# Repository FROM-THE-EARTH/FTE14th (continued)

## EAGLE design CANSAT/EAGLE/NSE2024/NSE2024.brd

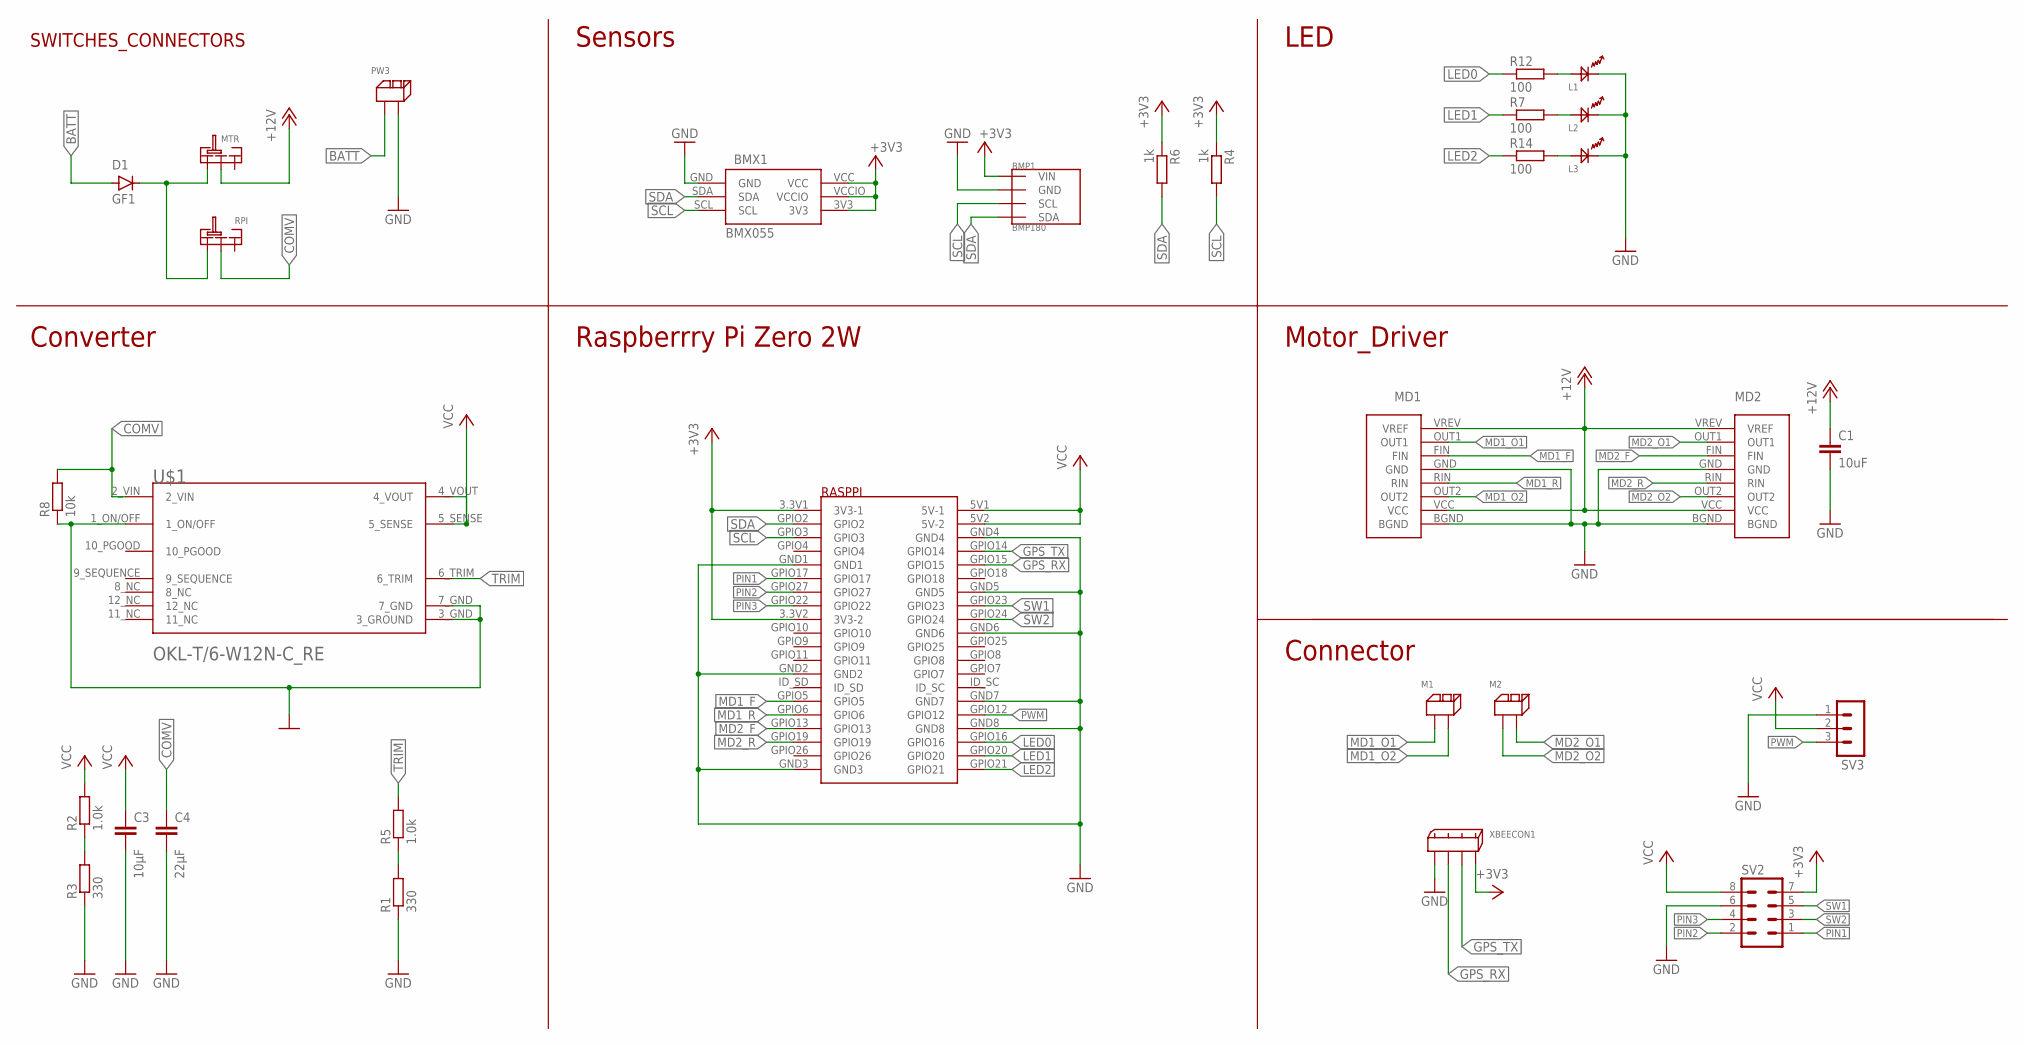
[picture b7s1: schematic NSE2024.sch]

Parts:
BMP1: BMP180; GY-68
BMX1: BMX055
C1: 10uF; C0603
C3: 10μF; C0603
C4: 22μF; C0805
D1: GF1; SMA-DO214AC
L1, L2, L3: OSXX1608C1A
M1, M2: 2PIN
MD1, MD2: BD6222HFP-TR
MTR: SRIDE_SWITCH
PW3: 2PIN
R1, R3: 330; R0603
R2, R5: 1.0k; R0603
R4, R6: 1k; R0603
R7, R12, R14: 100; R0603
R8: 10k; R0603
RASPPI: RASPBERYPIZEROW
RPI: SRIDE_SWITCH
SV2: MA04-2
SV3: MA03-1
U$1: OKL-T/6-W12N-C_RE; MURATA_IKL-T-6-W12N-C_0_RECOMENDED
XBEECON1: 2.5_MINI-SPOX_4PIN

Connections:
+3V3: BMP1.P1 (VIN), BMX1.3V3, BMX1.VCC, BMX1.VCCIO, R4.1, R6.1, RASPPI.3.3V1 (3V3-1), RASPPI.3.3V2 (3V3-2), SV2.7, XBEECON1.P$4 (4)
+5V: C3.1, U$1.4_VOUT, U$1.5_SENSE
+12V: C1.1, MD1.VCC, MD1.VREV (VREF), MD2.VCC, MD2.VREV (VREF), MTR.LR
BATT: D1.A, PW3.P$1
COMV: C4.1, R8.2, RPI.LR, U$1.2_VIN
GND: BMP1.P2 (GND), BMX1.GND, C1.2, C3.2, C4.2, L1.CT, L2.CT, L3.CT, MD1.BGND, MD1.GND, MD2.BGND, MD2.GND, PW3.P$2, R1.1, R3.1, R8.1, RASPPI.GND1, RASPPI.GND2, RASPPI.GND3, RASPPI.GND4, RASPPI.GND5, RASPPI.GND6, RASPPI.GND7, RASPPI.GND8, SV2.6, SV3.1, U$1.1_ON/OFF, U$1.3_GND (3_GROUND), U$1.7_GND, XBEECON1.P$1 (1)
GPS_RX: RASPPI.GPIO15, XBEECON1.P$2 (2)
GPS_TX: RASPPI.GPIO14, XBEECON1.P$3 (3)
LED0: R12.1, RASPPI.GPIO16
LED1: R7.1, RASPPI.GPIO20
LED2: R14.1, RASPPI.GPIO21
MD1_F: MD1.FIN, RASPPI.GPIO5
MD1_O1: M1.P$1, MD1.OUT1
MD1_O2: M1.P$2, MD1.OUT2
MD1_R: MD1.RIN, RASPPI.GPIO6
MD2_F: MD2.FIN, RASPPI.GPIO13
MD2_O1: M2.P$2, MD2.OUT1
MD2_O2: M2.P$1, MD2.OUT2
MD2_R: MD2.RIN, RASPPI.GPIO19
unnamed: R1.2, R5.1
unnamed: R2.1, R3.2
unnamed: L1.AN, R12.2
unnamed: D1.K (C), MTR.L, RPI.L
unnamed: L3.AN, R14.2
unnamed: L2.AN, R7.2
PIN1: RASPPI.GPIO17, SV2.1
PIN2: RASPPI.GPIO27, SV2.2
PIN3: RASPPI.GPIO22, SV2.4
PWM: RASPPI.GPIO12, SV3.3
SCL: BMP1.P3 (SCL), BMX1.SCL, R4.2, RASPPI.GPIO3
SDA: BMP1.P4 (SDA), BMX1.SDA, R6.2, RASPPI.GPIO2
SW1: RASPPI.GPIO23, SV2.5
SW2: RASPPI.GPIO24, SV2.3
TRIM: R5.2, U$1.6_TRIM
VCC: R2.2, RASPPI.5V1 (5V-1), RASPPI.5V2 (5V-2), SV2.8, SV3.2

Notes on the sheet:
SWITCHES_CONNECTORS
Sensors
Converter
Motor_Driver
LED
Connector
Raspberrry Pi Zero 2W

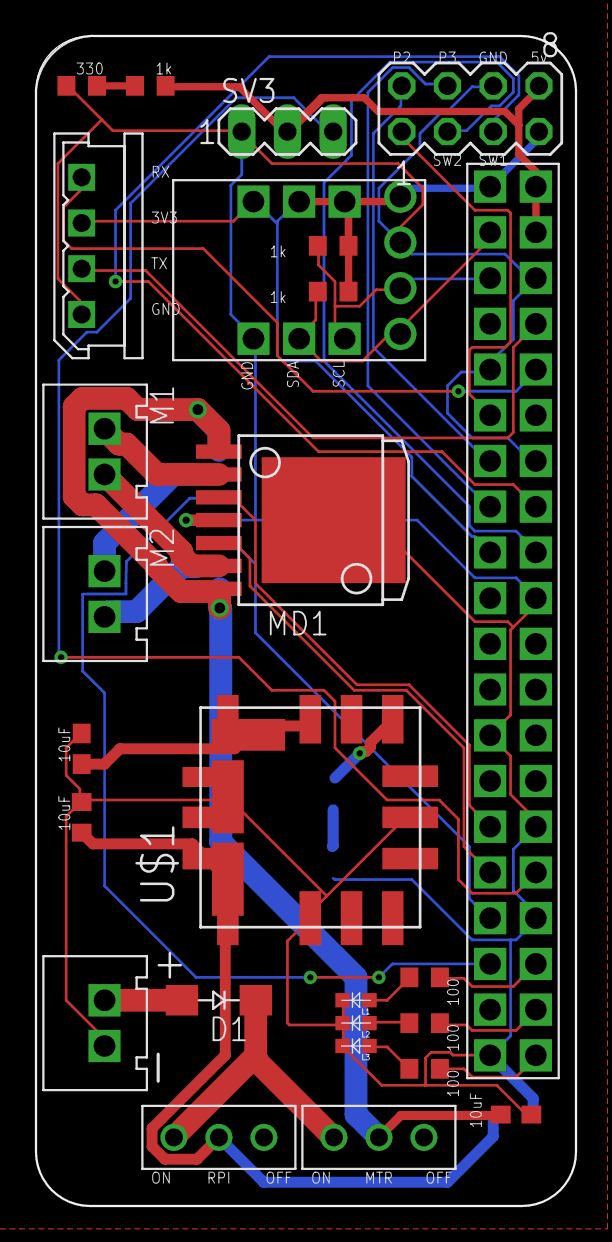
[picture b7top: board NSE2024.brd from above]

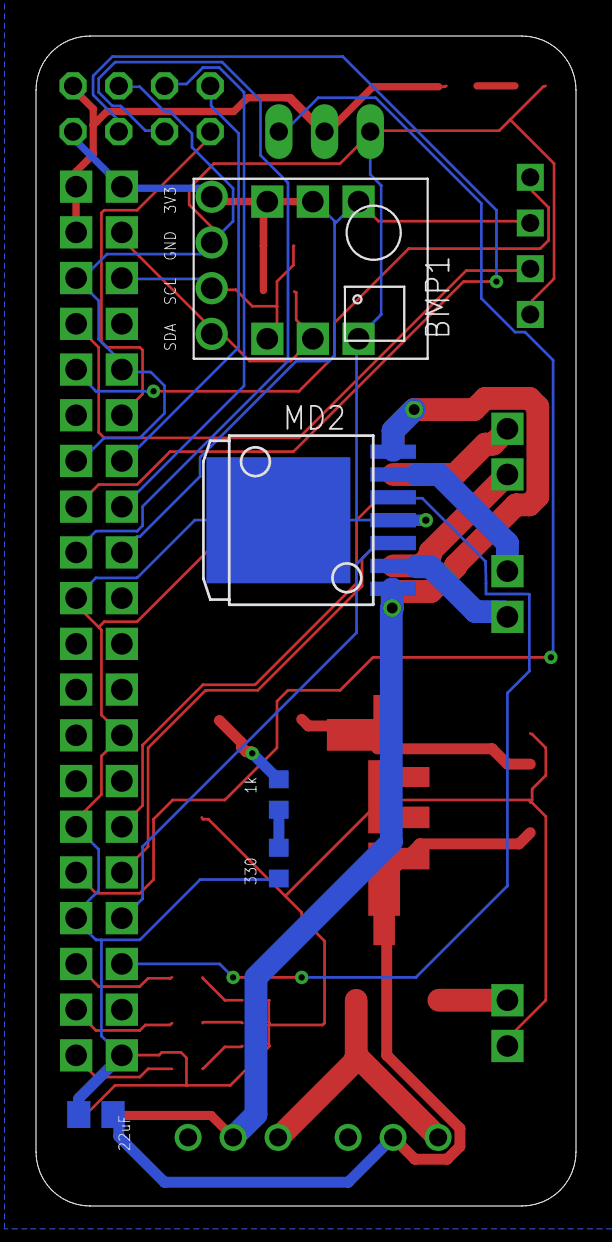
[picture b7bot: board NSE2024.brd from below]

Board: 2 copper layers, 30.0 x 65.0 mm, 31 parts (5 on the bottom side), 35 nets.

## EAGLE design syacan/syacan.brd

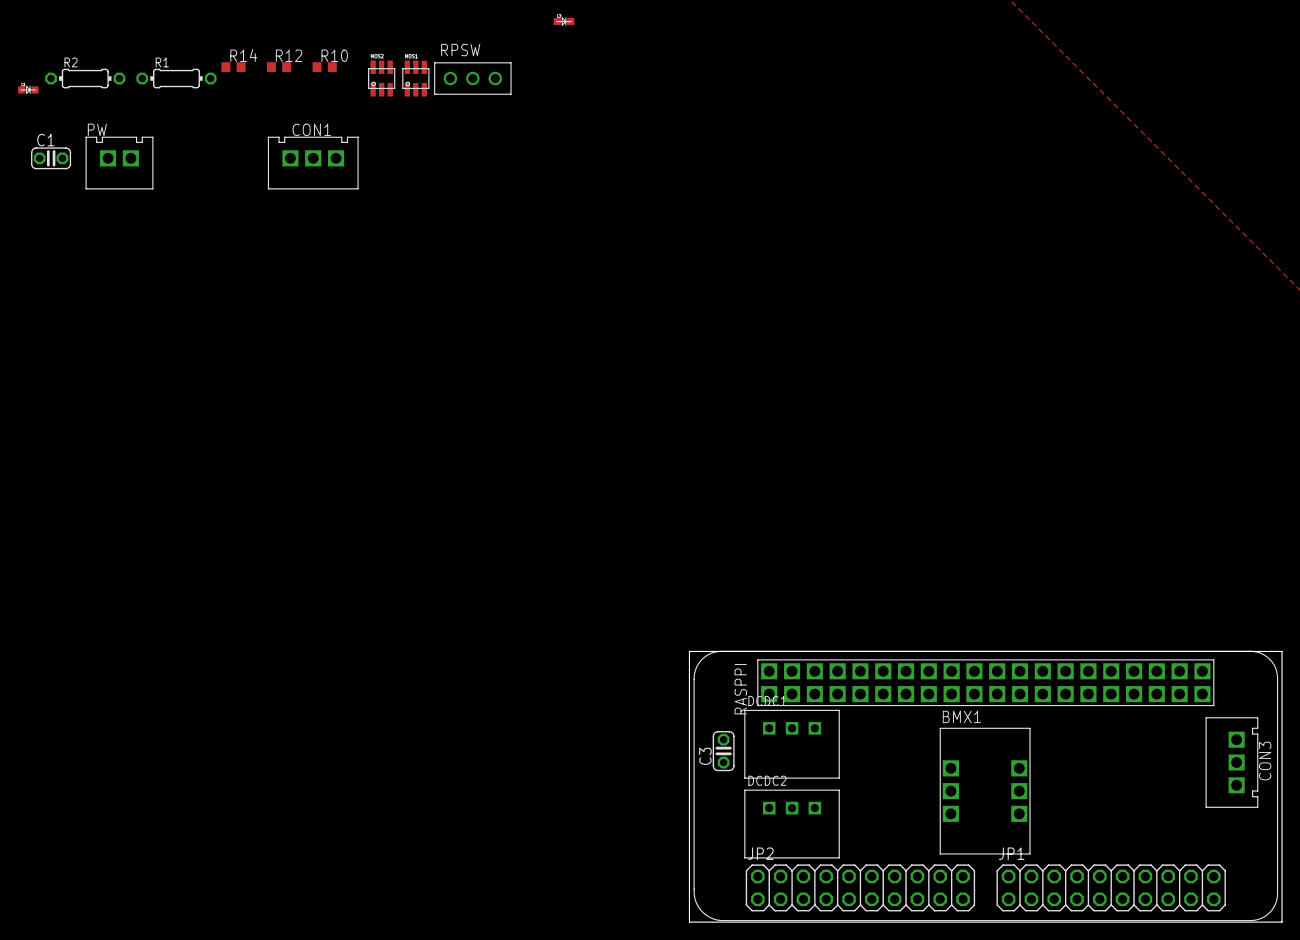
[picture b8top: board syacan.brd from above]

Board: 2 copper layers, 66.0 x 30.1 mm, 21 parts (0 on the bottom side), 35 nets, no tracks yet.

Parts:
BMX1: BMX055
C1, C3: 3.3uF; C025-024X044
CON1, CON3: 3PIN
DCDC1, DCDC2: 3.3V1A_M78AR033-1
JP1, JP2: 2X10
L1, L3: OSXX1608C1A
MOS1, MOS2: SSM6J808R
PW: 2PIN
R1, R2: 4.7k; 0204/7
R10: 100k; R0603
R12, R14: 100; R0603
RASPPI: RASPBERYPIZEROW
RPSW: SRIDE_SWITCH

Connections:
+3V3: C1.1, DCDC1.VOUT, JP2.1, RASPPI.3.3V1, RASPPI.3.3V2
+5V: BMX1.VCC, C3.1, CON1.P$2, CON3.P$2, DCDC1.VIN, DCDC2.VOUT, JP2.2, R1.2, R2.2, RASPPI.5V1, RASPPI.5V2
+7.4V: MOS2.1, MOS2.2, MOS2.5, MOS2.6
BATT: MOS1.1, MOS1.2, MOS1.5, MOS1.6, PW.P$2
GND: BMX1.GND, C1.2, C3.2, CON1.P$3, CON3.P$3, DCDC1.GND, DCDC2.GND, JP2.5, JP2.6, JP2.7, JP2.8, L1.CT, L3.CT, MOS1.3, PW.P$1, RASPPI.GND1, RASPPI.GND2, RASPPI.GND3, RASPPI.GND4, RASPPI.GND5, RASPPI.GND6, RASPPI.GND7, RPSW.LR
GPIO4: JP1.1, RASPPI.GPIO4
GPIO5: JP1.3, RASPPI.GPIO5
GPIO6: JP1.5, RASPPI.GPIO6
GPIO7: JP1.7, RASPPI.GPIO7
GPIO8: JP1.9, RASPPI.GPIO8
GPIO9: JP1.11, RASPPI.GPIO9
GPIO10: JP1.13, RASPPI.GPIO10
GPIO11: JP1.15, RASPPI.GPIO11
GPIO13: JP1.2, RASPPI.GPIO13
GPIO14: JP1.4, RASPPI.GPIO14
GPIO15: JP1.6, RASPPI.GPIO15
GPIO16: JP1.8, RASPPI.GPIO16
GPIO17: JP1.10, RASPPI.GPIO17
GPIO19: JP1.12, RASPPI.GPIO19
GPIO20: JP1.16, RASPPI.GPIO20
GPIO21: JP1.14, RASPPI.GPIO21
GPIO23: JP1.17, RASPPI.GPIO23
GPIO24: JP1.19, RASPPI.GPIO24
GPIO25: JP1.18, RASPPI.GPIO25
GPIO27: JP1.20, RASPPI.GPIO27
LED0: R12.1, RASPPI.GPIO22
LED2: R14.1, RASPPI.GPIO26
unnamed: L1.AN, R12.2
unnamed: L3.AN, R14.2
unnamed: MOS1.4, MOS2.4, R10.2
unnamed: MOS2.3, R10.1, RPSW.L
SCL: BMX1.SCL, JP2.11, R1.1, RASPPI.GPIO3
SDA: BMX1.SDA, JP2.9, R2.1, RASPPI.GPIO2
SV0: CON3.P$1, RASPPI.GPIO12
SV2: CON1.P$1, RASPPI.GPIO18

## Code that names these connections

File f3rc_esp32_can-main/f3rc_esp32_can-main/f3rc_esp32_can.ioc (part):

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Mcu.Name=STM32G474R(B-C-E)Tx
Mcu.Package=LQFP64
Mcu.UserName=STM32G474RBTx
PA11.Mode=FDCAN_Activate
PA11.Signal=FDCAN1_RX
PA12.Mode=FDCAN_Activate
PA12.Signal=FDCAN1_TX
PA2.Mode=Asynchronous
PA2.Signal=USART2_TX
PA3.Mode=Asynchronous
PA3.Signal=USART2_RX
PC4.Mode=Asynchronous
PC4.Signal=USART1_TX
PC5.Mode=Asynchronous
PC5.Signal=USART1_RX
RCC.HSE_VALUE=8000000
RCC.SYSCLKFreq_VALUE=80000000
RCC.SYSCLKSource=RCC_SYSCLKSOURCE_PLLCLK
board=custom

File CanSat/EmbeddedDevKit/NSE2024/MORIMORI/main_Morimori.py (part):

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DATA_SAMPLING_RATE = 0.00001
ALTITUDE_CONST1 = 30
ALTITUDE_CONST2 = 5
SERVO_PIN = 12
LED0 = 25
LED1 = 8
LED2 = 7
HIGH = 1
LOW = 0
M1A = 13
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
bmx = BMX055.BMX055()
bmp = BMP085.BMP085()
servo = pigpio.pi()

nowTime = datetime.datetime.now()
fileName = '/home/karisora/FTE14/NiCs2024/log/testlog_' + nowTime.strftime('%Y-%m%d-%H%M%S') + '.csv'
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    bmx.setUp()

    GPIO.setmode(GPIO.BCM)
    GPIO.setup(LED1, GPIO.OUT)
    GPIO.setup(LED2, GPIO.OUT)
   #GPIO.setup(SW1, GPIO.IN, pull_up_down=GPIO.PUD_DOWN)
   #GPIO.setup(SW2, GPIO.IN, pull_up_down=GPIO.PUD_DOWN)
    GPIO.setup(Heating_wire, GPIO.OUT)          
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    roi_img = cv2.cvtColor(roi_img, cv2.COLOR_BGR2RGB)
    detector.set_roi_img(roi_img)

    GPIO.output(LED2, HIGH)
    print("Setup OK")


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            after = currentMilliTime()
        if (max[1] - min[1]) > 20 and (max[2] - min[2] > 20):
            print("calibration(): Complete!")
            GPIO.output(LED1, HIGH)
            complete = True
            time.sleep(1)
            calibBias[1] = (max[1] + min[1]) / 2
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
            calibRange[1] = (max[1] - min[1]) / 2
            calibRange[2] = (max[2] - min[2]) / 2
            GPIO.output(LED1, LOW)
            time.sleep(2)


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    # 角度を500から2500のパルス幅にマッピングする
    pulse_width = (angle / 180) * (2500 - 500) + 500
    # パルス幅を設定してサーボを回転させる
    servo.set_servo_pulsewidth(SERVO_PIN, pulse_width)

def LED_Checker(num):
    for _ in range(num):
        GPIO.output(LED1, HIGH)
        time.sleep(0.1)
        GPIO.output(LED1, LOW)
        time.sleep(0.1)


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
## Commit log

2023-11-13 ki
    k
2023-11-14 test
2023-11-16 ver1.1
2023-11-19 Create NiCs_cansat
2023-11-27 Create NiCs2024
2023-11-27 rename
2023-11-27 ver1.3
2023-12-21 opencv_test を更新
2024-02-15 Create ISE2024_14thboard#1.1.b##
2024-03-16 add remote_main.py
2024-03-29 a
    a
2024-03-30 upload result files
2024-04-05 カラーコーン到達判定を改良・コメント付記
2024-04-26 q
    a
2024-05-06 i
    u
2024-05-12 NiCs2024の基盤追加
2024-05-12 ファイル整理
2024-05-12 NSE2024基盤追加
2024-06-04 board追加
2024-06-24 Create dengen1.2.sch
    new dengen
2024-06-25 n ew
2024-06-27 Checked and created board file
2024-06-27 Created dengen board file
2024-06-27 Board changed
2024-06-27 328修正
2024-06-28 2枚版追加
2024-06-30 Changed dengen board
2024-07-02 changed board files
2024-07-03 Changed board file
2024-07-03 Changed board
2024-07-04 Completed board files ver1.0
2024-07-04 ver1.1 uploaded
2024-07-04 ver1.2
2024-07-05 Added via
2024-07-10 add readme about raspi setup
2024-07-12 readme
2024-07-12 k
    k
2024-07-12 add readme
2024-07-12 completed datalogger 4.1
2024-07-13 completed ver4.1
2024-07-14 changed v4.2
2024-07-16 ver4.1 flight model
2024-07-16 add excel and .Rmd file for flightdata analysis
2024-08-06 NSE2024
2024-08-06 cv2 add
2024-08-06 stuck試し
2024-08-06 added
2024-08-07 Flag
2024-08-07 Flag_v2
2024-08-09 timeout.v1
2024-08-09 morimori
2024-08-12 add modified Prologue
2024-08-23 fix file structures
2024-08-23 Upload ipynb files for aerodynamics
2024-09-05 フォトカプラ
2024-12-25 code
2025-02-18 gimbal
2025-12-10 update file
